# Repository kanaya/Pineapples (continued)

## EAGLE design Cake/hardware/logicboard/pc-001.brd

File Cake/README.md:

# PineappleCake

PineappleCake is a set of add-on board and software for [Arduino MKR1000](https://store.arduino.cc/usa/arduino-mkr1000) series for attaching analog sensors. Coupled with MKR1000, PineappleCake can read up-to seven physical sensors and send the values via HTTP on WiFi.

You can also attach [triple-axis accelerometer](https://www.sparkfun.com/products/12756) on PineappleCake. The acceleration data can be accessible via wireless HTTP connection.

And one more thing, you can control a couple of LEDs also via wireless HTTP connection.

You can change the IP address of multiple PineappleCakes by using attached rotary switch so that you’ll never need to modify the source code for just changing the addresses.

PineappleCake also offers missing [I2C connector (+5V, D7, SCL, SDA, GND)](https://store.arduino.cc/usa/arduino-mkrzero) found in other MKR series (e.g. [MKR ZERO](https://store.arduino.cc/usa/arduino-mkrzero)).

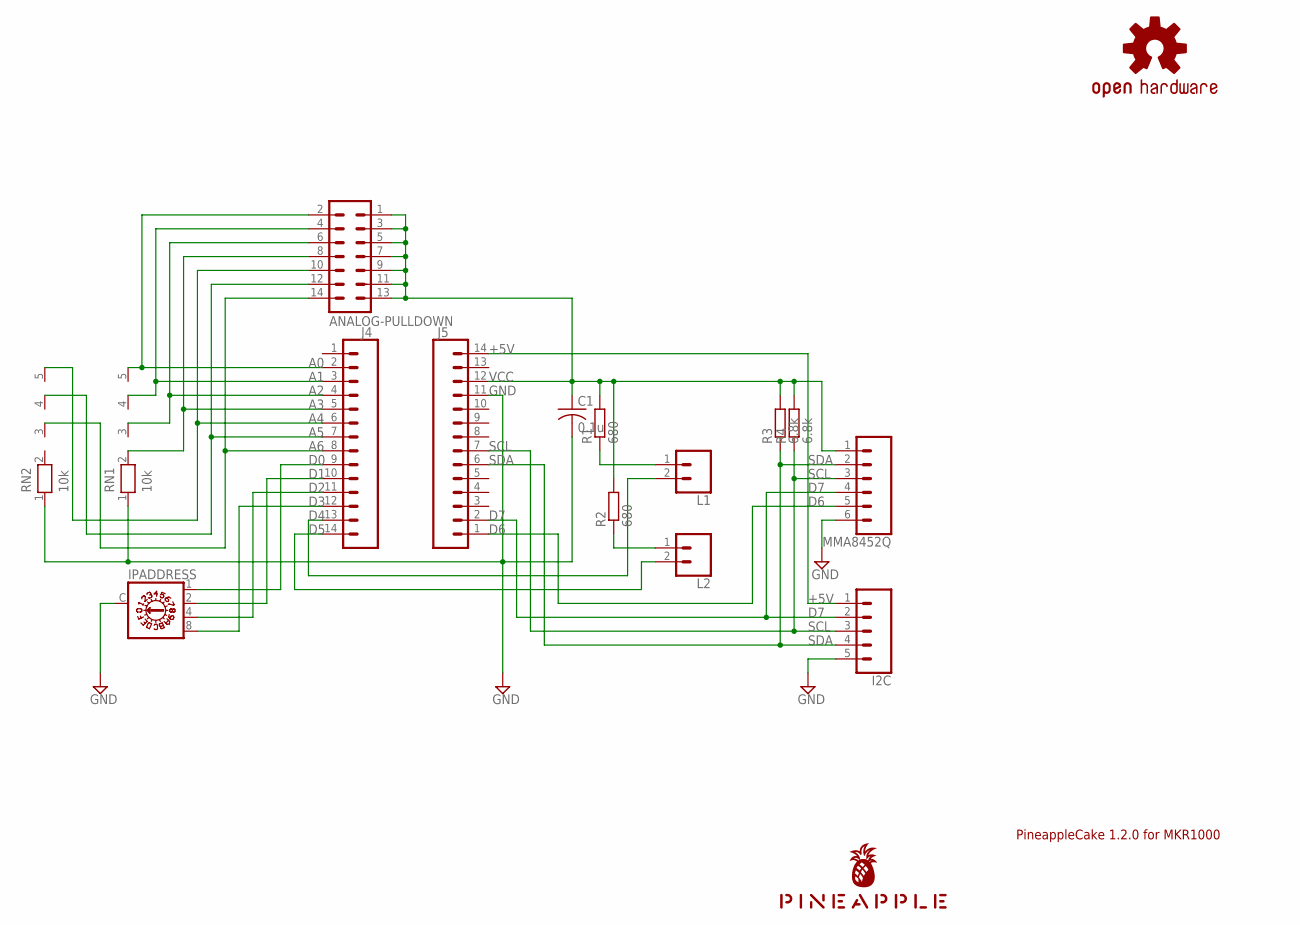
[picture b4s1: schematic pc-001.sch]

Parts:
ANALOG-PULLDOWN: ML14L
C1: 0.1u; C025-025X050
I2C: CONN_05SMD; 1X05_1MM
IPADDRESS: A1353HEX
J4, J5: DNP; 1X14
L1, L2: CONN_02-JST-2-PTH-NO_SILK; JST-2-PTH-NS
LOGO1: OSHW-LOGOS-COPPER; OSHW-LOGO-S_COPPER
MMA8452Q: CONN_06NO_SILK_FEMALE_PTH; 1X06_NO_SILK
R1, R2: 680; 0204/5
R3, R4: 6.8k; 0204/5
RN1, RN2: 10k; RN-5
U$1: PINEAPPLE450

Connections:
+5V: I2C.1, J5.14
A0: ANALOG-PULLDOWN.2, J4.2, RN1.5
A1: ANALOG-PULLDOWN.4, J4.3, RN1.4
A2: ANALOG-PULLDOWN.6, J4.4, RN1.3
A3: ANALOG-PULLDOWN.8, J4.5, RN1.2
A4: ANALOG-PULLDOWN.10, J4.6, RN2.5
A5: ANALOG-PULLDOWN.12, J4.7, RN2.4
A6: ANALOG-PULLDOWN.14, J4.8, RN2.3
D0: IPADDRESS.1, J4.9
D1: IPADDRESS.2, J4.10
D2: IPADDRESS.4, J4.11
D3: IPADDRESS.8, J4.12
D4: J4.13, L1.2
D5: J4.14, L2.2
D6: J5.1, MMA8452Q.5
D7: I2C.2, J5.2, MMA8452Q.4
GND: C1.2, I2C.5, IPADDRESS.C, J5.11, MMA8452Q.6, RN1.1, RN2.1
LED1A: L1.1, R1.1
LED2A: L2.1, R2.1
SCL: I2C.3, J5.7, MMA8452Q.3, R4.1
SDA: I2C.4, J5.6, MMA8452Q.2, R3.1
VCC: ANALOG-PULLDOWN.1, ANALOG-PULLDOWN.3, ANALOG-PULLDOWN.5, ANALOG-PULLDOWN.7, ANALOG-PULLDOWN.9, ANALOG-PULLDOWN.11, ANALOG-PULLDOWN.13, C1.1, J5.12, MMA8452Q.1, R1.2, R2.2, R3.2, R4.2

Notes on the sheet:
PineappleCake 1.2.0 for MKR1000

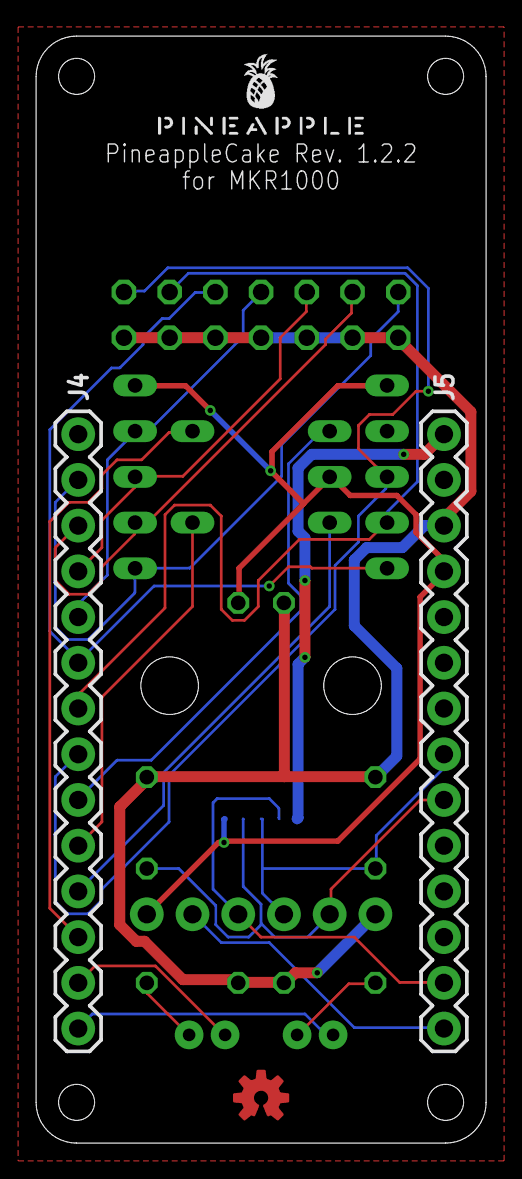
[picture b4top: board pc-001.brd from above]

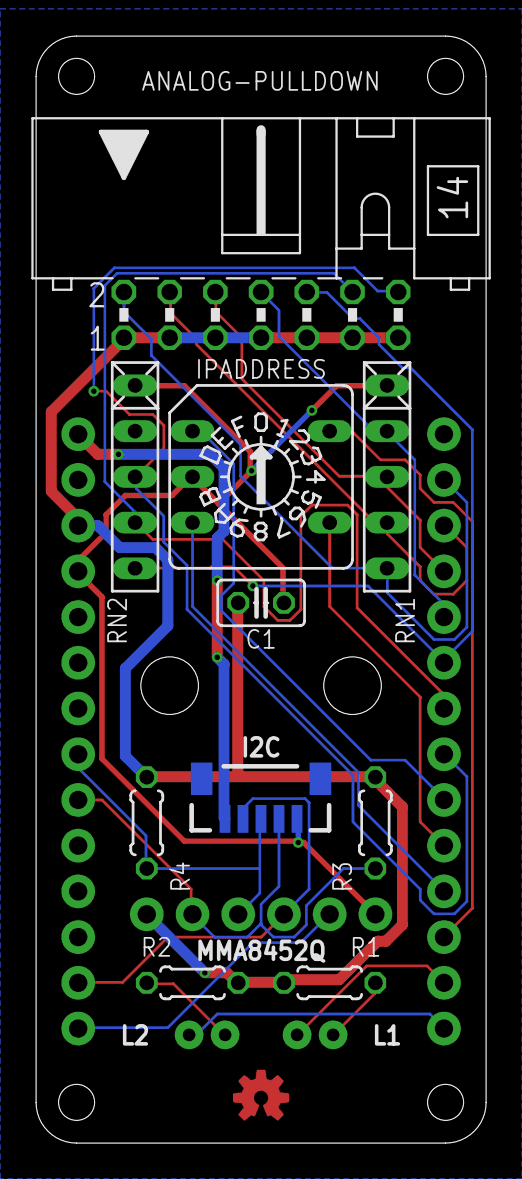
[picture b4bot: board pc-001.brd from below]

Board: 2 copper layers, 25.0 x 61.5 mm, 17 parts (13 on the bottom side), 22 nets.

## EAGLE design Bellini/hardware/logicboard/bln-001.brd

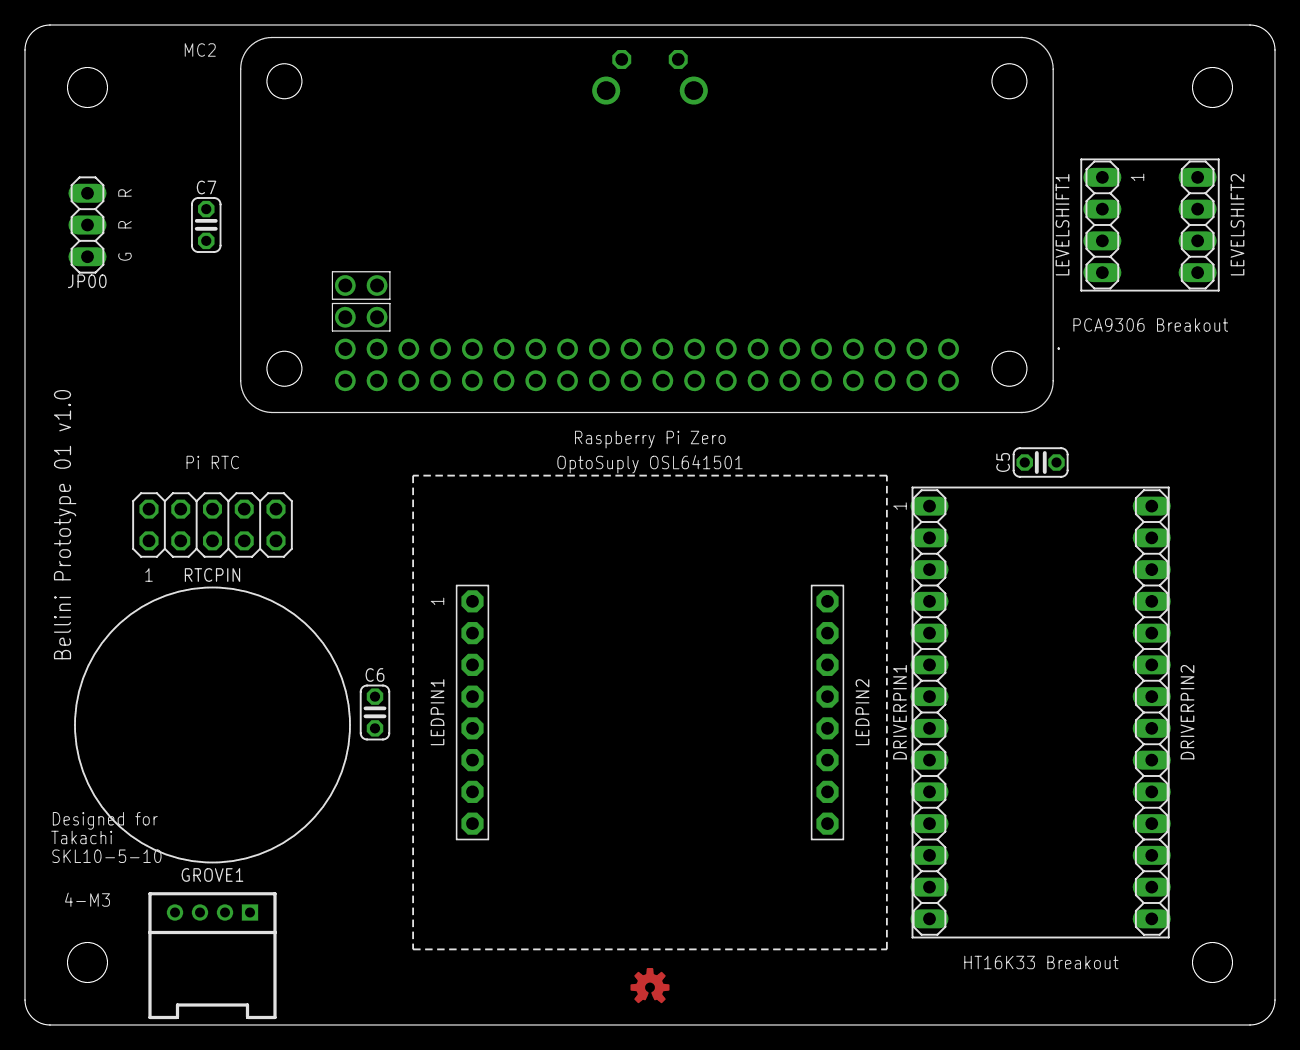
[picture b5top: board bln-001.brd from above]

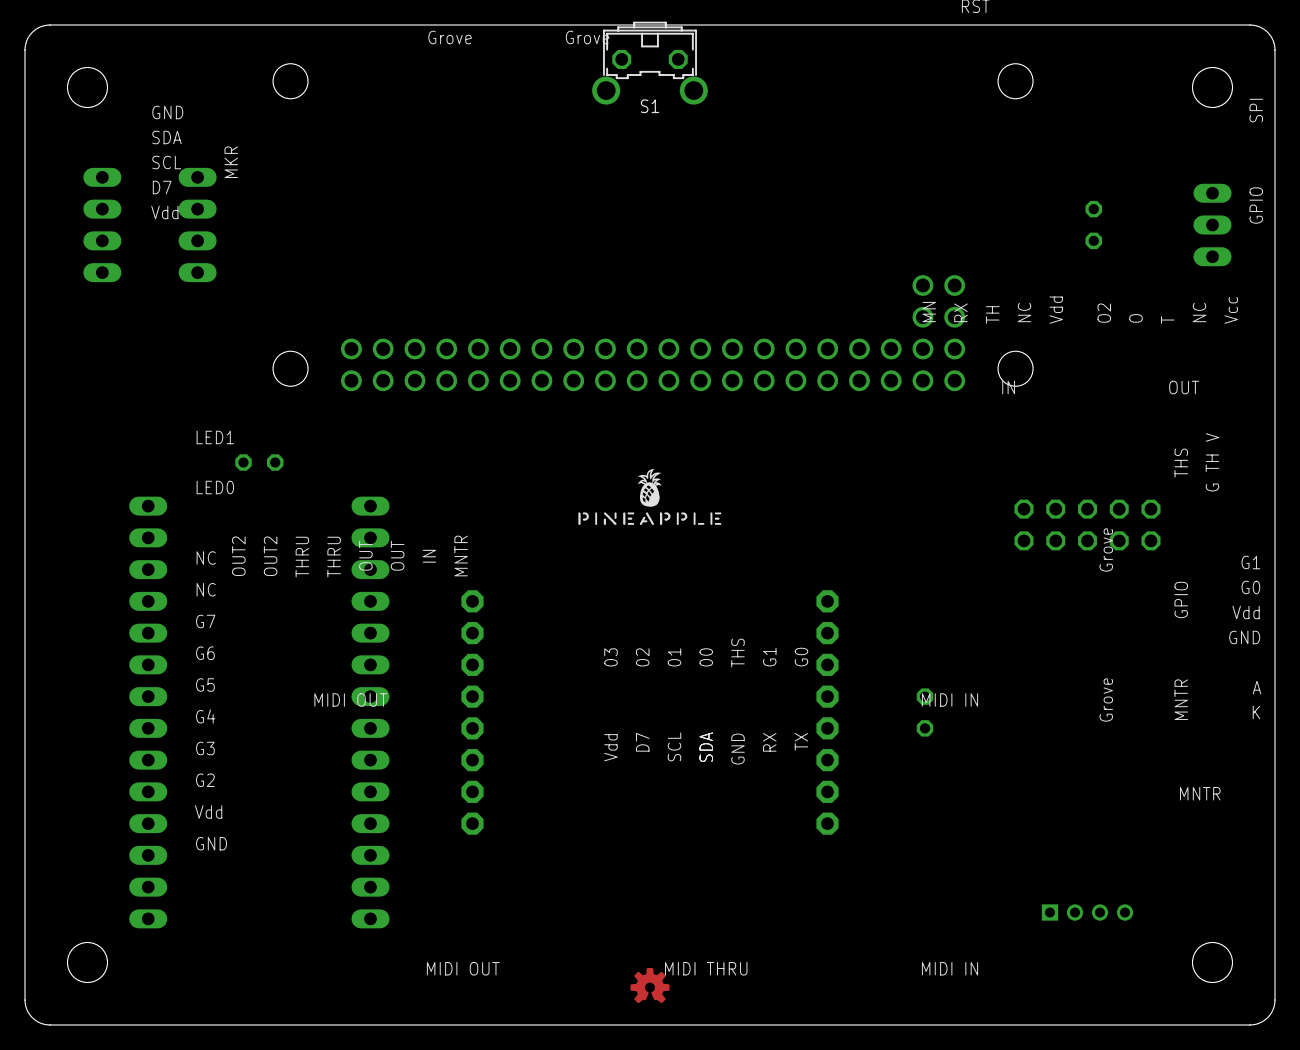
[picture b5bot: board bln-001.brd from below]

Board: 2 copper layers, 100.0 x 80.0 mm, 16 parts (2 on the bottom side), 27 nets, no tracks yet.

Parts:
C5, C6: 10n; C025-024X044
C7: 100n; C025-024X044
DRIVERPIN1, DRIVERPIN2: 1X14
GROVE1: Grove; 4P-2.0-90D
JP00: RST; 1X03
LEDPIN1, LEDPIN2: 1X08-BIG
LEVELSHIFT1, LEVELSHIFT2: 1X04
LOGO1: OSHW-LOGOS-COPPER; OSHW-LOGO-S_COPPER
MC2: RASPBERRY_PI_ZERO_W_(V1.3); RASPBERRYPIZEROWV13
RTCPIN: 2X05
S1: RST; B3F-31XX
U$1: PINEAPPLE450_SILK

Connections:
A0: DRIVERPIN2.11, LEDPIN2.5
A1: DRIVERPIN2.10, LEDPIN1.3
A2: DRIVERPIN2.9, LEDPIN1.4
A3: DRIVERPIN2.8, LEDPIN2.2
A4: DRIVERPIN2.7, LEDPIN1.6
A5: DRIVERPIN2.6, LEDPIN2.3
A6: DRIVERPIN2.5, LEDPIN2.7
A7: DRIVERPIN2.4, LEDPIN2.8
C0: DRIVERPIN1.2, LEDPIN2.1
C1: DRIVERPIN1.3, LEDPIN2.6
C2: DRIVERPIN1.4, LEDPIN1.8
C3: DRIVERPIN1.5, LEDPIN2.4
C4: DRIVERPIN1.6, LEDPIN1.1
C5: DRIVERPIN1.7, LEDPIN1.7
C6: DRIVERPIN1.8, LEDPIN1.2
C7: DRIVERPIN1.9, LEDPIN1.5
DIGITAL7: MC2.26, RTCPIN.7
GND: C5.2, C6.2, C7.2, DRIVERPIN1.1, GROVE1.4, JP00.1, LEVELSHIFT2.1, MC2.6, MC2.9, MC2.14, MC2.20, MC2.30, MC2.34, MC2.39, RTCPIN.6, RTCPIN.9, S1.1
RST: JP00.2, JP00.3, S1.2
RX: MC2.10, RTCPIN.10
SCL: GROVE1.1, LEVELSHIFT1.2, MC2.5, RTCPIN.5
SCL5V: DRIVERPIN2.12, LEVELSHIFT2.3
SDA: GROVE1.2, LEVELSHIFT1.3, MC2.3, RTCPIN.3
SDA5V: DRIVERPIN2.13, LEVELSHIFT2.2
TX: MC2.8, RTCPIN.8
VCC: DRIVERPIN2.14, LEVELSHIFT2.4, MC2.2, MC2.4, RTCPIN.2, RTCPIN.4
VDD: C5.1, C6.1, C7.1, GROVE1.3, LEVELSHIFT1.1, MC2.1, MC2.17, RTCPIN.1

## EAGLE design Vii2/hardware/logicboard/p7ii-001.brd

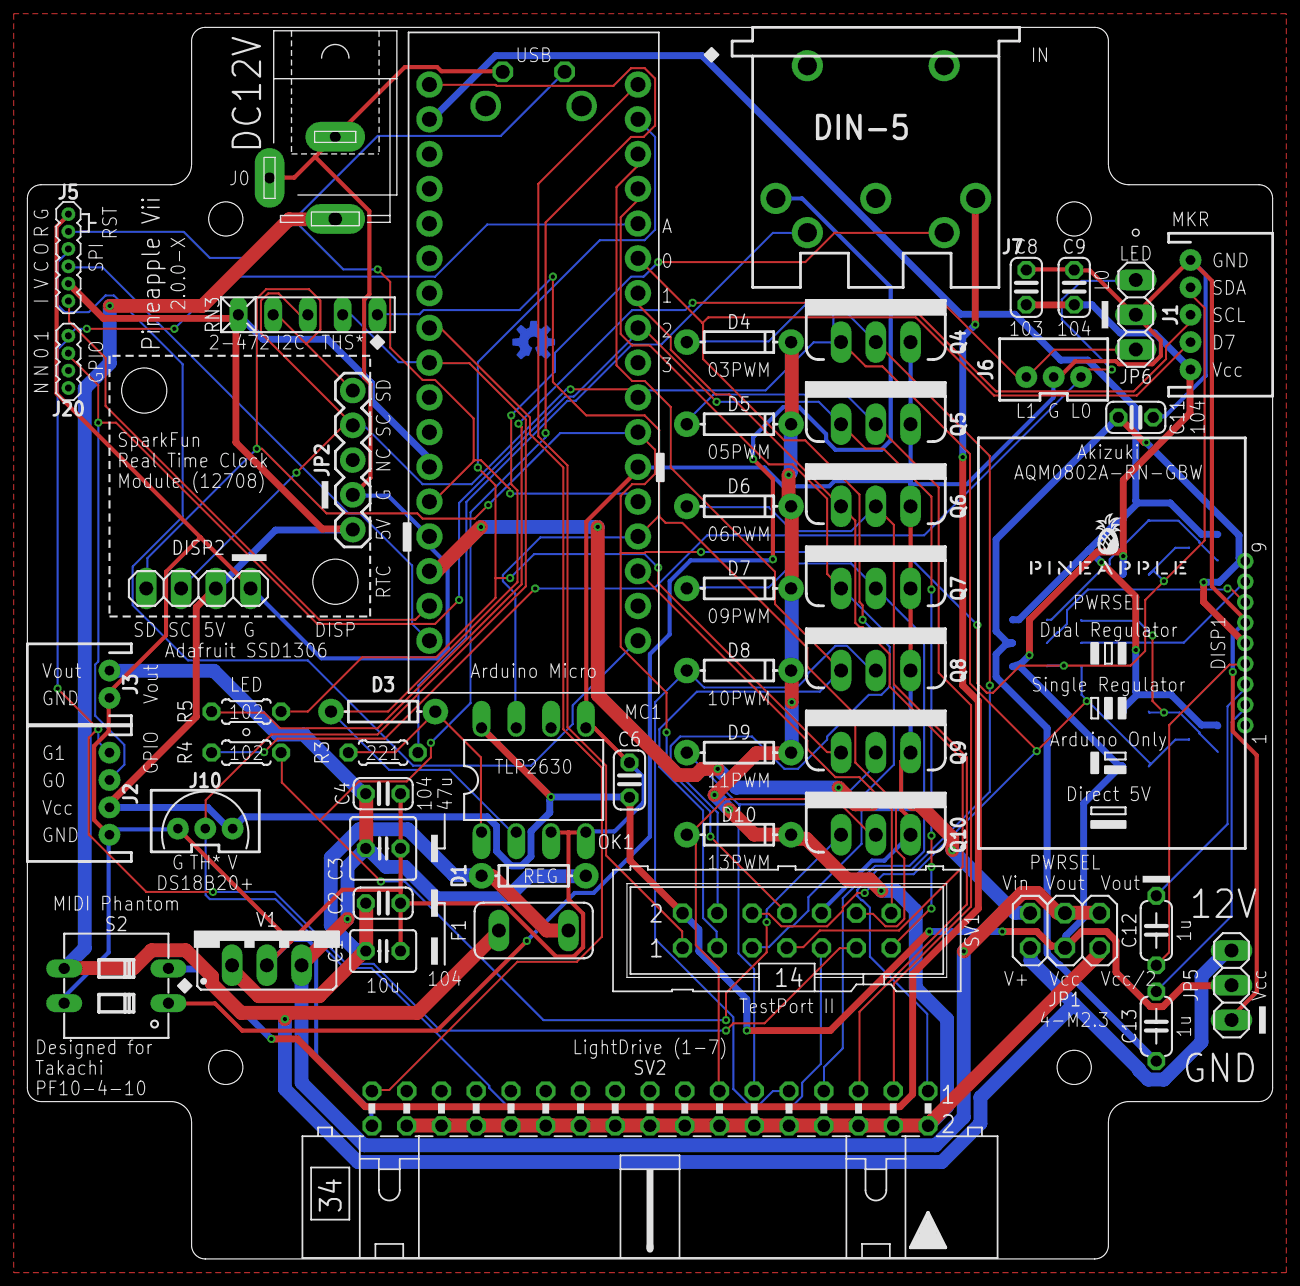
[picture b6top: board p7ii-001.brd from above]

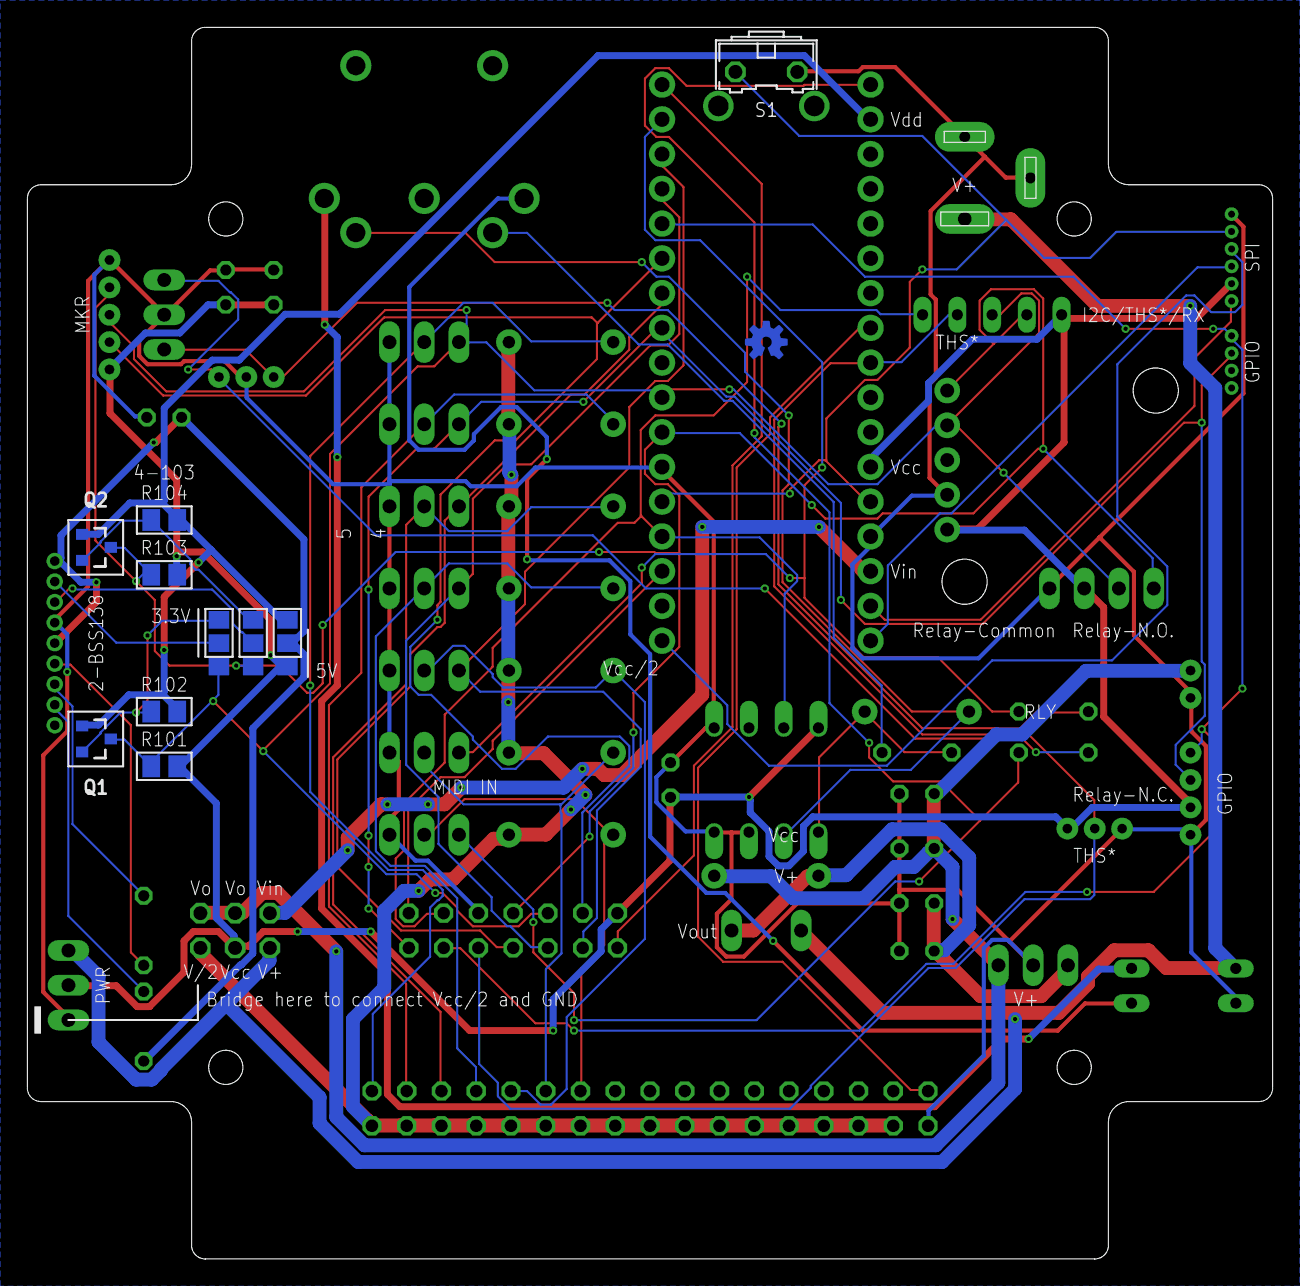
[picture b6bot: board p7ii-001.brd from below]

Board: 2 copper layers, 91.0 x 90.0 mm, 66 parts (11 on the bottom side), 49 nets.

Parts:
C1: 10u; C025-030X050
C2, C4, C9, C11: 100n; C025-024X044
C3: 47u; C025-050X050
C6, C8: 10n; C025-024X044
C12, C13: 1u; C050-024X044
D1, D3: DIODE-1N4148
D4, D5, D6, D7, D8, D9, D10: 200mA/100V/1V; DIODE-1N4148
DISP1: AQM0802A-RN-GBW; AQM0802A-RN-GBW-FOOTPRINT
DISP2: MNTR; 1X04
F1: 1.8A; TE5
H1, H2: STAND-OFF
J0: SPC4077
J1: MKR; JST-5-PTH
J2: GPIO; JST-4-PTH
J3: Vcc; JST-2-PTH
J5: SPI; 1X06_1.27MM
J6: LED; JST-3-PTH-VERT
J7: DIN5; DIN5-RA-PTH
J10: 1-Wire; JST-3-PTH-VERT
J20: GPIO; 1X04_1.27MM
JMP1, JMP2, JMP3: 0R-JUMPA; A0R-JMP
JP1: PWRSEL; 2X03
JP2: RTC; 1X05
JP5: PWR; 1X03
JP6: LED; 1X03
LOGO1: OSHW-LOGOS-COPPER; OSHW-LOGO-S_COPPER
MC1: ARDUINOMICRO
OK1: HCPL2630; DIL08
Q1, Q2: 220mA/50V/3.5Ω; SOT23-3
Q4, Q5, Q6, Q7, Q8, Q9, Q10: 60V/32A/35mΩ; TO220V
R3: 220; 0204/5
R4, R5: 1k; 0204/5
R101, R102, R103, R104: 10k; M2012
RN3: 4.7k; RN-5
S1: RST; B3F-31XX
S2: DIP02YL
SV1: ML14
SV2: ML34L
U$1: PINEAPPLE450_SILK
V1: 5V; 78XXS

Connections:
CAP1N: C12.2, DISP1.3
CAP1P: C12.1, DISP1.4
D7GATE: J1.4, MC1.P$6, SV1.4
DTCT0: MC1.P$7, Q6.1, SV1.7
DTCT1: MC1.P$4, Q7.1, SV1.5
DTCT2: MC1.P$3, Q8.1, SV1.3
DTCT3: MC1.P$1, SV1.1
GND: C1.2, C2.2, C3.2, C4.2, C6.2, C8.2, C9.2, C11.2, DISP1.6, DISP2.1, J0.1, J0.2, J1.1, J2.1, J3.1, J5.6, J6.2, J10.1, JP2.2, JP5.1, JP6.2, MC1.P$12, MC1.P$21, OK1.3, OK1.4, OK1.5, Q4.3, Q5.3, Q6.3, Q7.3, Q8.3, Q9.3, Q10.3, S1.1, S2.4, SV1.10, SV2.34, V1.GND
GPIO0: J2.3, J20.3, MC1.P$8, Q5.1, SV1.13
GPIO1: J2.4, J20.4, MC1.P$5, SV1.11
LCDVOUT: C13.2, DISP1.2
LD00: D4.A, Q4.2, SV2.1
LD01: D5.A, Q5.2, SV2.3
LD02: D6.A, Q6.2, SV2.5
LD03: D7.A, Q7.2, SV2.7
LD04: D8.A, Q8.2, SV2.9
LD05: D9.A, Q9.2, SV2.11
LD06: D10.A, Q10.2, SV2.13
LED0: MC1.P$34, Q10.1, R4.2
LED0A: J6.3, JP6.3, R4.1
LED1: MC1.P$2, Q9.1, R5.2
LED1A: J6.1, JP6.1, R5.1
MIDIINGND: J7.1, S2.1
MIDIINSND: D3.C, OK1.1, R3.1
MIDIINV+: J7.3, S2.2
MIRTN: D3.A, J7.5, OK1.2
MISND: J7.4, R3.2
MISO: J5.1, MC1.P$19
MNTR: MC1.P$27, SV2.33
MOSI: J5.4, MC1.P$17
RST: J5.5, MC1.P$13, MC1.P$22, S1.2
RX: MC1.P$14, OK1.7, RN3.5, SV1.12
SCK: J5.3, MC1.P$18
SCL: DISP2.3, J1.3, JMP3.3, JP2.4, MC1.P$10, Q1.3, Q4.1, R101.1, RN3.3, SV1.6
SCL3V: JMP3.1, Q1.2, R102.1
SCL3V/5V: DISP1.8, JMP3.2
SDA: DISP2.4, J1.2, JMP2.3, JP2.5, MC1.P$11, Q2.3, R103.1, RN3.2, SV1.8
SDA3V: JMP2.1, Q2.2, R104.1
SDA3V/5V: DISP1.7, JMP2.2
THS: J10.2, MC1.P$26, RN3.4, SV1.9
TX: MC1.P$15, SV1.14
V+: F1.1, J0.3, JP1.1, JP5.3, S2.3
VCC: C6.1, C8.1, C9.1, DISP2.2, J1.5, J2.2, J5.2, J10.3, JMP1.3, JP1.3, JP2.1, JP5.2, MC1.P$23, OK1.8, R101.2, R103.2, RN3.1, SV1.2
VCC/2: D4.C, D5.C, D6.C, D7.C, D8.C, D9.C, D10.C, JP1.5, SV2.2, SV2.4, SV2.6, SV2.8, SV2.10, SV2.12, SV2.14, SV2.16, SV2.18, SV2.20, SV2.22, SV2.24, SV2.26, SV2.28, SV2.30, SV2.32
VDD: JMP1.1, MC1.P$33, Q1.1, Q2.1, R102.2, R104.2
VDD/VCC: C11.1, C13.1, DISP1.5, DISP1.9, JMP1.2
VIN: JP1.2, MC1.P$20
VIN0: C1.1, C2.1, D1.C, F1.2, V1.IN
VOUT: C3.1, C4.1, D1.A, J3.2, JP1.4, JP1.6, V1.OUT

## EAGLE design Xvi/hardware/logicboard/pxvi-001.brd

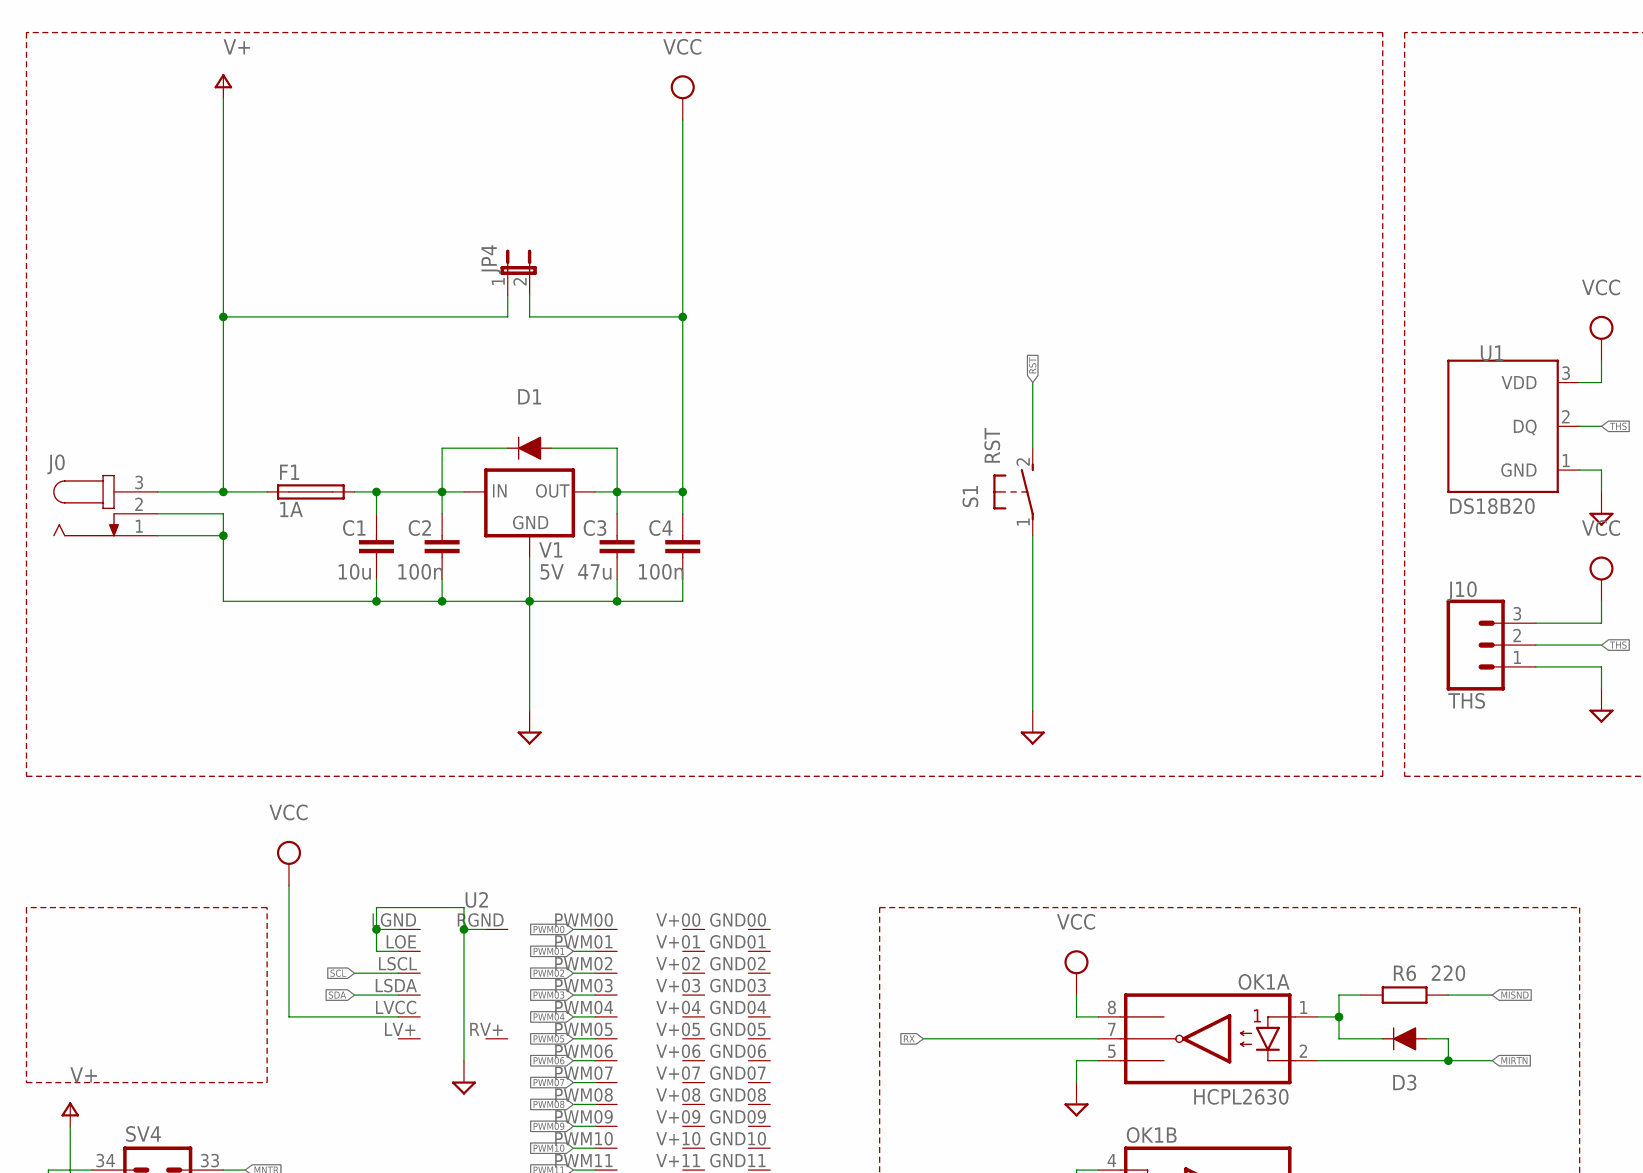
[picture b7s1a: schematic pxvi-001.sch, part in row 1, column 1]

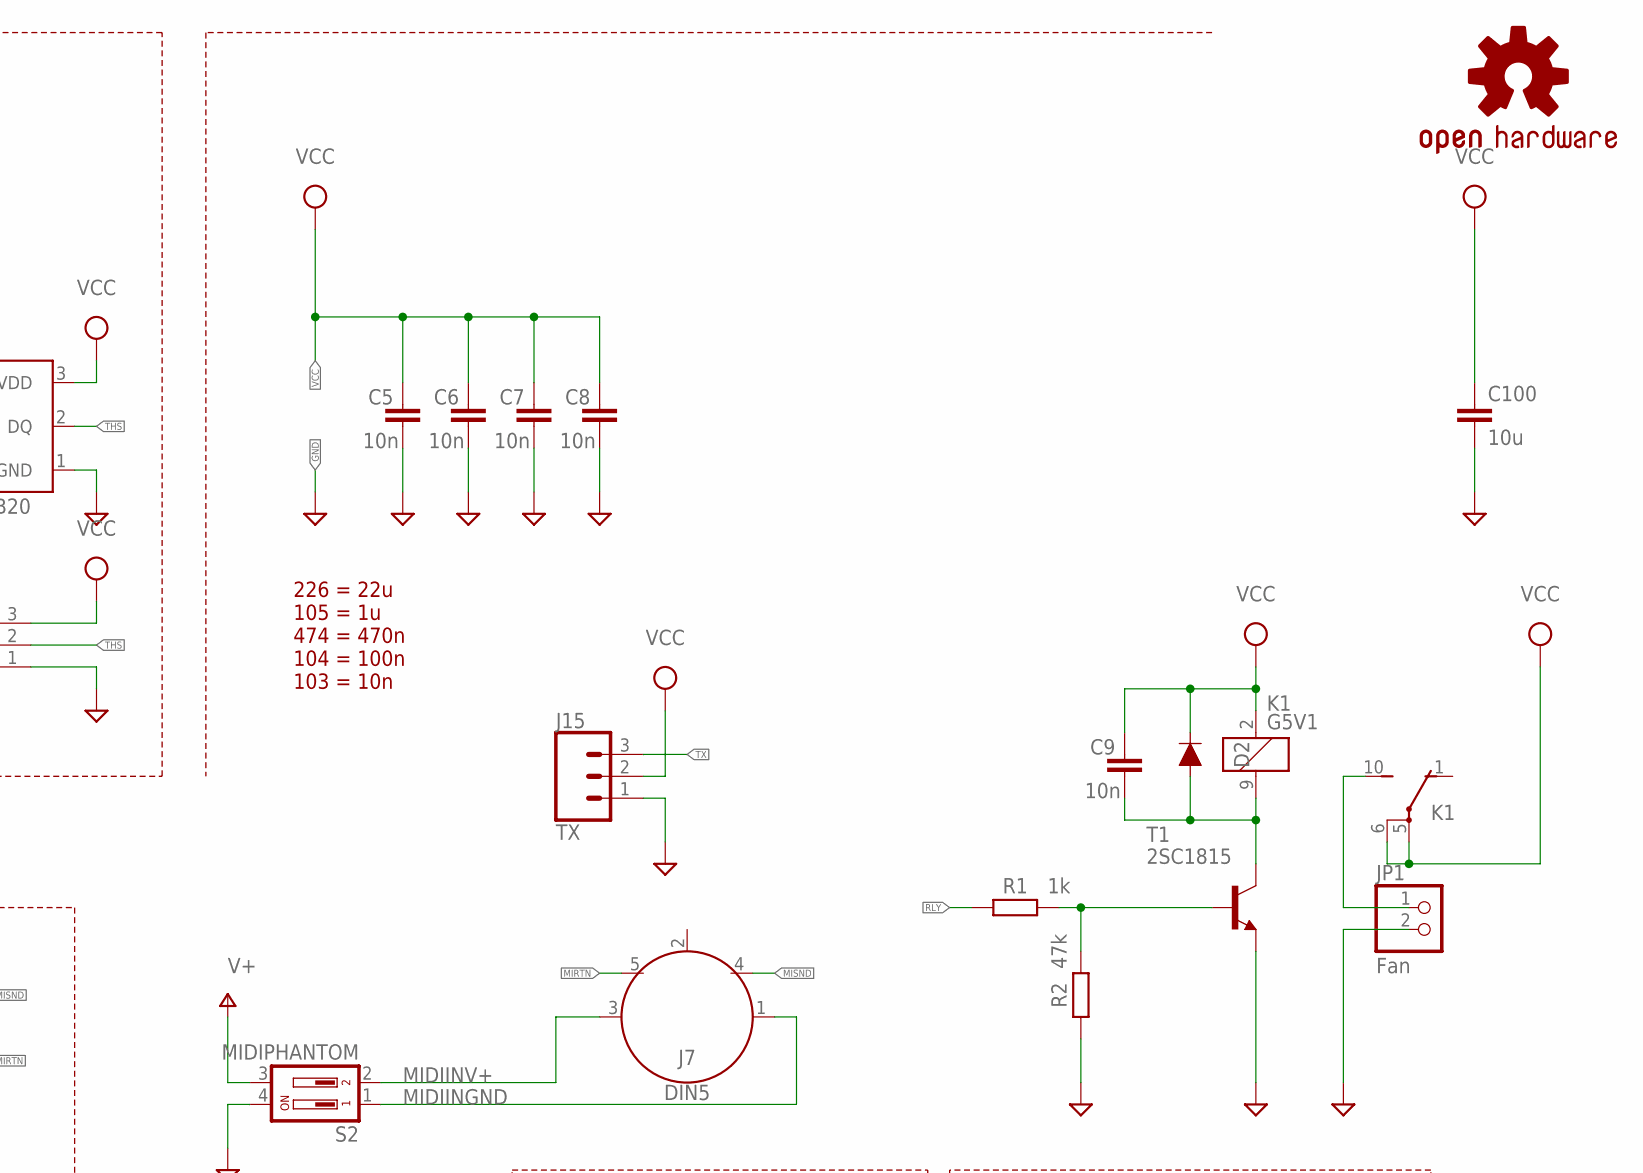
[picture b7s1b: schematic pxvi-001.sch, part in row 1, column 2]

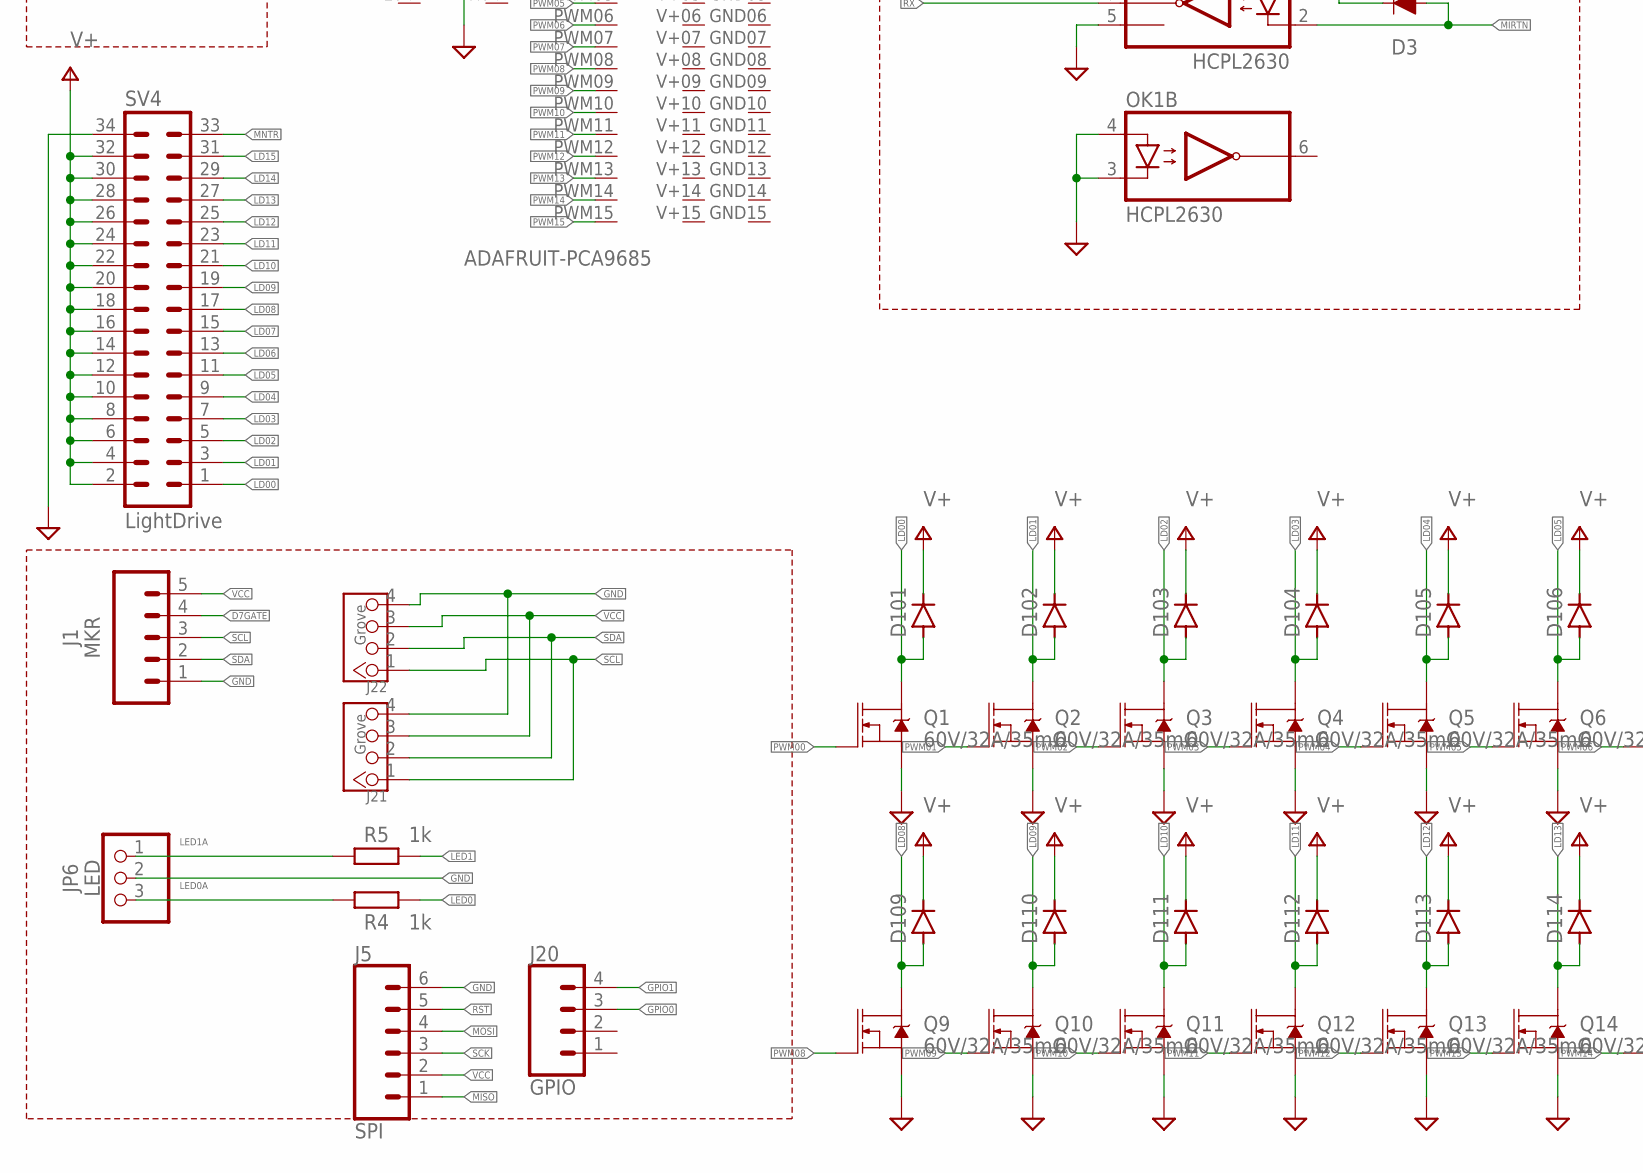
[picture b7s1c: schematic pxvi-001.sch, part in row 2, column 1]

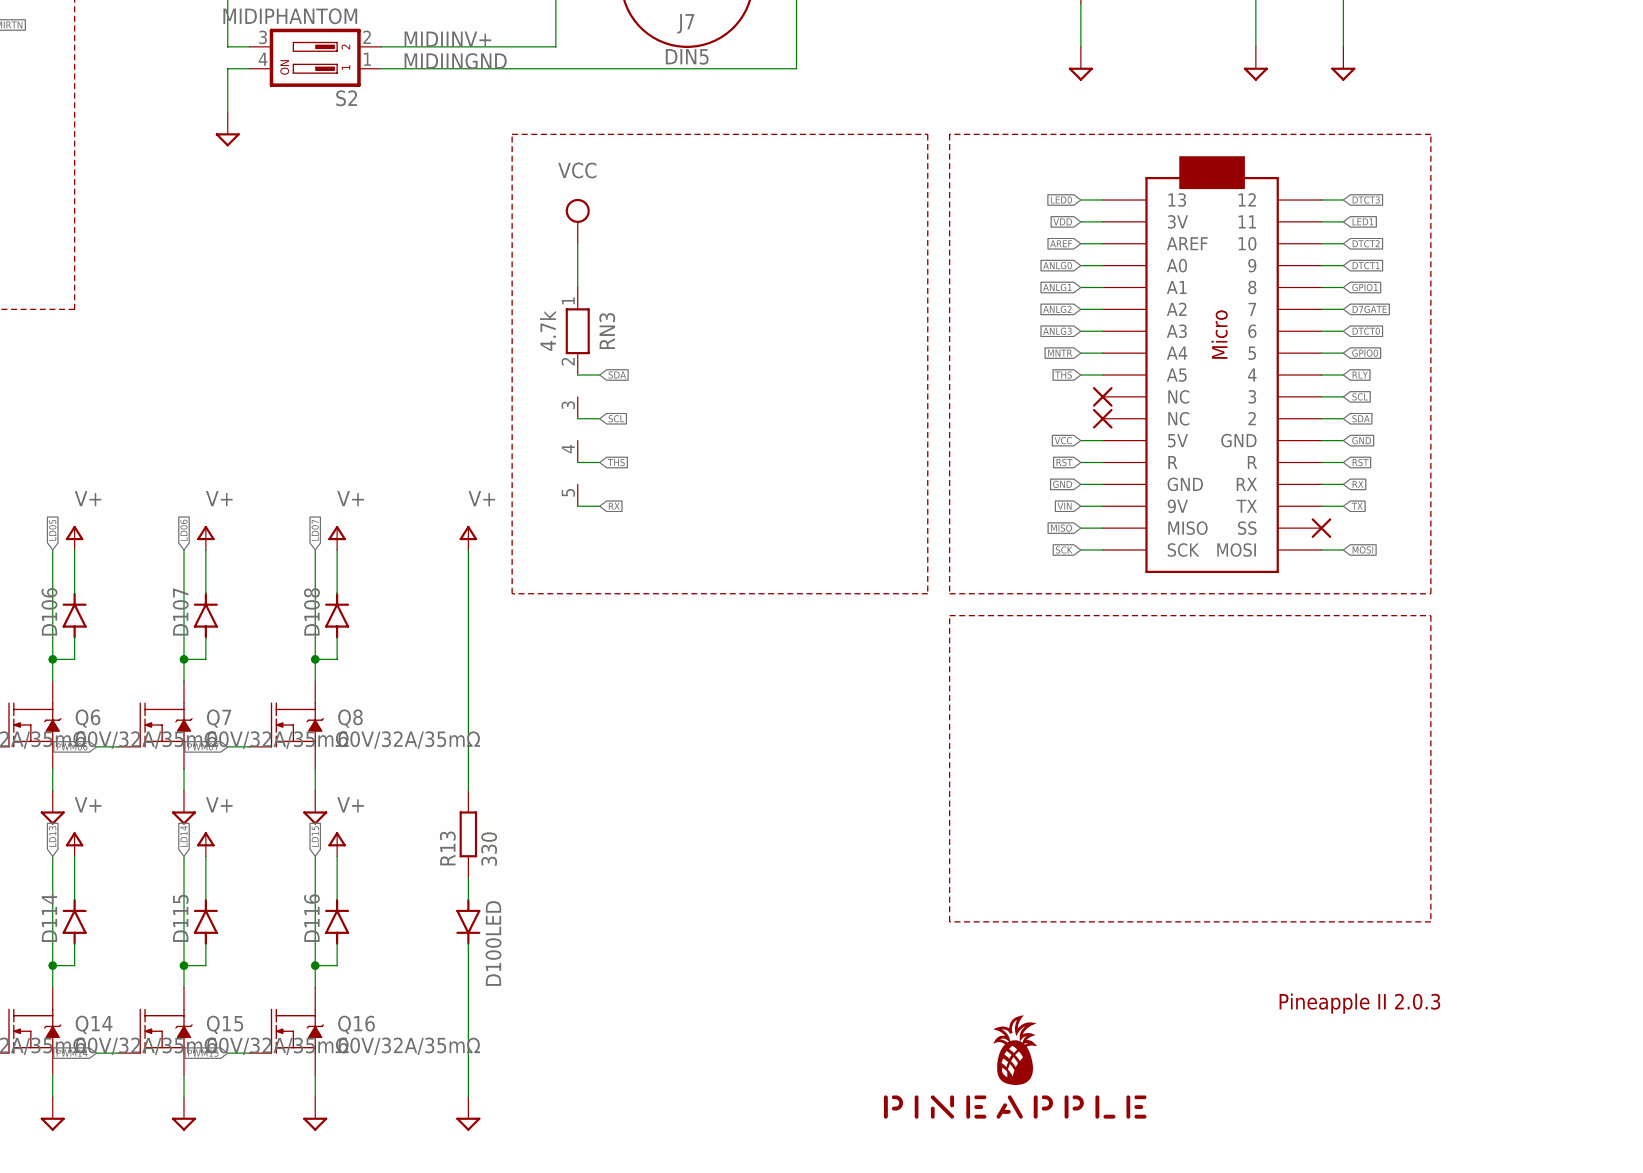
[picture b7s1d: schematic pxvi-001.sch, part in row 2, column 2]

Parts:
C1: 10u; C025-024X044
C2, C4: 100n; C025-030X050
C3: 47u; C025-050X050
C5, C6, C7, C8, C9: 10n; C025-024X044
C100: 10u; C3216
D1, D2, D3: DIODE-1N4148
D100LED, D101, D102, D103, D104, D105, D106, D107, D108, D109, D110, D111, D112, D113, D114, D115, D116: CGRM400-G; SOD-123_MINI-SMA
F1: 1A; TE5
J0: JACK-PLUG0; SPC4077
J1: MKR; JST-5-PTH
J5: SPI; 1X06_1.27MM
J7: DIN5; DIN5-RA-PTH
J10: THS; JST-3-PTH
J15: TX; JST-3-PTH-VERT
J20: GPIO; 1X04_1.27MM
J21, J22: Grove; 4P-2.0-90D
JP1: Fan; 1X02
JP4: JP1E; JP1
JP6: LED; 1X03
K1: G5V1
LOGO1: OSHW-LOGOS-COPPER; OSHW-LOGO-S_COPPER
MC1: ARDUINOMICRO
OK1: HCPL2630; DIL08
Q1, Q2, Q3, Q4, Q5, Q6, Q7, Q8, Q9, Q10, Q11, Q12, Q13, Q14, Q15, Q16: 60V/32A/35mΩ; TO220V
R1, R4, R5: 1k; 0204/5
R2: 47k; 0204/5
R6: 220; 0204/5
R13: 330; R3216
RN3: 4.7k; RN-5
S1: RST; B3F-31XX
S2: MIDIPHANTOM; DIP02YL
SV4: LightDrive; ML34L
T1: 2SC1815; TO92-ECB
U1: DS18B20; TO-92-AMMO
U2: ADAFRUIT-PCA9685; ADAFRUIT-PCA9685-FOOTPRINT
U$1: PINEAPPLE450_SILK
V1: 5V; 78XXS

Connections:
ANLG0: MC1.P$31 (A0)
ANLG1: MC1.P$30 (A1)
ANLG2: MC1.P$29 (A2)
ANLG3: MC1.P$28 (A3)
AREF: MC1.P$32 (AREF)
D7GATE: J1.4, MC1.P$6 (7)
D100A: D100LED.A, R13.1
DTCT0: MC1.P$7 (6)
DTCT1: MC1.P$4 (9)
DTCT2: MC1.P$3 (10)
DTCT3: MC1.P$1 (12)
FAN: JP1.1, K1.10 (S)
GND: C1.2, C2.2, C3.2, C4.2, C5.2, C6.2, C7.2, C8.2, C100.2, D100LED.C, J0.1, J0.2, J1.1, J5.6, J10.1, J15.1, J21.4, J22.4, JP1.2, JP6.2, MC1.P$12 (GND), MC1.P$21 (GND), OK1.3 (C2), OK1.4 (A2), OK1.5 (GND), Q1.3 (S), Q2.3 (S), Q3.3 (S), Q4.3 (S), Q5.3 (S), Q6.3 (S), Q7.3 (S), Q8.3 (S), Q9.3 (S), Q10.3 (S), Q11.3 (S), Q12.3 (S), Q13.3 (S), Q14.3 (S), Q15.3 (S), Q16.3 (S), R2.1, S1.1, S2.4, SV4.34, T1.E, U1.1 (GND), U2.LGND (1), U2.LOE (2), U2.RGND (7), V1.GND
GPIO0: J20.3, MC1.P$8 (5)
GPIO1: J20.4, MC1.P$5 (8)
LD00: D101.A, Q1.2 (D), SV4.1
LD01: D102.A, Q2.2 (D), SV4.3
LD02: D103.A, Q3.2 (D), SV4.5
LD03: D104.A, Q4.2 (D), SV4.7
LD04: D105.A, Q5.2 (D), SV4.9
LD05: D106.A, Q6.2 (D), SV4.11
LD06: D107.A, Q7.2 (D), SV4.13
LD07: D108.A, Q8.2 (D), SV4.15
LD08: D109.A, Q9.2 (D), SV4.17
LD09: D110.A, Q10.2 (D), SV4.19
LD10: D111.A, Q11.2 (D), SV4.21
LD11: D112.A, Q12.2 (D), SV4.23
LD12: D113.A, Q13.2 (D), SV4.25
LD13: D114.A, Q14.2 (D), SV4.27
LD14: D115.A, Q15.2 (D), SV4.29
LD15: D116.A, Q16.2 (D), SV4.31
LED0: MC1.P$34 (13), R4.2
LED0A: JP6.3, R4.1
LED1: MC1.P$2 (11), R5.2
LED1A: JP6.1, R5.1
MIDIINGND: J7.1, S2.1
MIDIINV+: J7.3, S2.2
MIRTN: D3.A, J7.5, OK1.2 (C1)
MISND: J7.4, R6.2
MISNDA: D3.C, OK1.1 (A1), R6.1
MISO: J5.1, MC1.P$19 (MISO)
MNTR: MC1.P$27 (A4), SV4.33
MOSI: J5.4, MC1.P$17 (MOSI)
PWM00: Q1.1 (G), U2.PWM00 (13)
PWM01: Q2.1 (G), U2.PWM01 (14)
PWM02: Q3.1 (G), U2.PWM02 (15)
PWM03: Q4.1 (G), U2.PWM03 (16)
PWM04: Q5.1 (G), U2.PWM04 (17)
PWM05: Q6.1 (G), U2.PWM05 (18)
PWM06: Q7.1 (G), U2.PWM06 (19)
PWM07: Q8.1 (G), U2.PWM07 (20)
PWM08: Q9.1 (G), U2.PWM08 (21)
PWM09: Q10.1 (G), U2.PWM09 (22)
PWM10: Q11.1 (G), U2.PWM10 (23)
PWM11: Q12.1 (G), U2.PWM11 (24)
PWM12: Q13.1 (G), U2.PWM12 (25)
PWM13: Q14.1 (G), U2.PWM13 (26)
PWM14: Q15.1 (G), U2.PWM14 (27)
PWM15: Q16.1 (G), U2.PWM15 (28)
RLY: MC1.P$9 (4), R1.1
RLYDRV: R1.2, R2.2, T1.B
RST: J5.5, MC1.P$13 (R), MC1.P$22 (R), S1.2 (S)
RX: MC1.P$14 (RX), OK1.7 (VO1), RN3.5
SCK: J5.3, MC1.P$18 (SCK)
SCL: J1.3, J21.1, J22.1, MC1.P$10 (3), RN3.3, U2.LSCL (3)
SDA: J1.2, J21.2, J22.2, MC1.P$11 (2), RN3.2, U2.LSDA (4)
THS: J10.2, MC1.P$26 (A5), RN3.4, U1.2 (DQ)
TX: J15.3, MC1.P$15 (TX)
V+: D101.C, D102.C, D103.C, D104.C, D105.C, D106.C, D107.C, D108.C, D109.C, D110.C, D111.C, D112.C, D113.C, D114.C, D115.C, D116.C, F1.1, J0.3, JP4.1, R13.2, S2.3, SV4.2, SV4.4, SV4.6, SV4.8, SV4.10, SV4.12, SV4.14, SV4.16, SV4.18, SV4.20, SV4.22, SV4.24, SV4.26, SV4.28, SV4.30, SV4.32
VCC: C3.1, C4.1, C5.1, C6.1, C7.1, C8.1, C9.1, C100.1, D1.A, D2.C, J1.5, J5.2, J10.3, J15.2, J21.3, J22.3, JP4.2, K1.2 (1), K1.5, K1.6, MC1.P$23 (5V), OK1.8 (VCC), RN3.1, U1.3 (VDD), U2.LVCC (5), V1.OUT
VDD: MC1.P$33 (3V)
VIN: MC1.P$20 (9V)
VREGIN: C1.1, C2.1, D1.C, F1.2, V1.IN
VRLY: C9.2, D2.A, K1.9 (2), T1.C

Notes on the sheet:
Pineapple II 2.0.3
226 = 22u 105 = 1u 474 = 470n 104 = 100n 103 = 10n
